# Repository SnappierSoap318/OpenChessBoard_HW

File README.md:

# OpenChessBoard_HW

## Overview
- OpenChessBoard_HW is an open-source hardware project aimed at creating a digital chessboard.
- This project includes the design and schematics for the main board, which can be used to build a functional chessboard.
- This project is derived from [OPEN_CHESS_BOARD](https://openchessboard.com/index.php/2023/03/21/the-openchessboard-design/)
- This project aims to make the design of the board more modular and tileable for ease of manufacturing

## Features
- Single tile design (make 32 white PCB's and 32 Black PCB's and you are done!)
- Uses the Arduino Nano ESP32 as the uP
- Least amount of pins used

## Getting Started
To get started with this project, follow these steps:
1. Clone the repository:
```bash
git clone https://github.com/SnappierSoap318/OpenChessBoard_HW.git
cd OpenChessBoard_HW
```
2. Open in KiCAD 7.0 or above.

## Contribution Guidelines 
If you'd like to contribute, please fork the repository and make a pull request and put the changes you have made as screenshots.

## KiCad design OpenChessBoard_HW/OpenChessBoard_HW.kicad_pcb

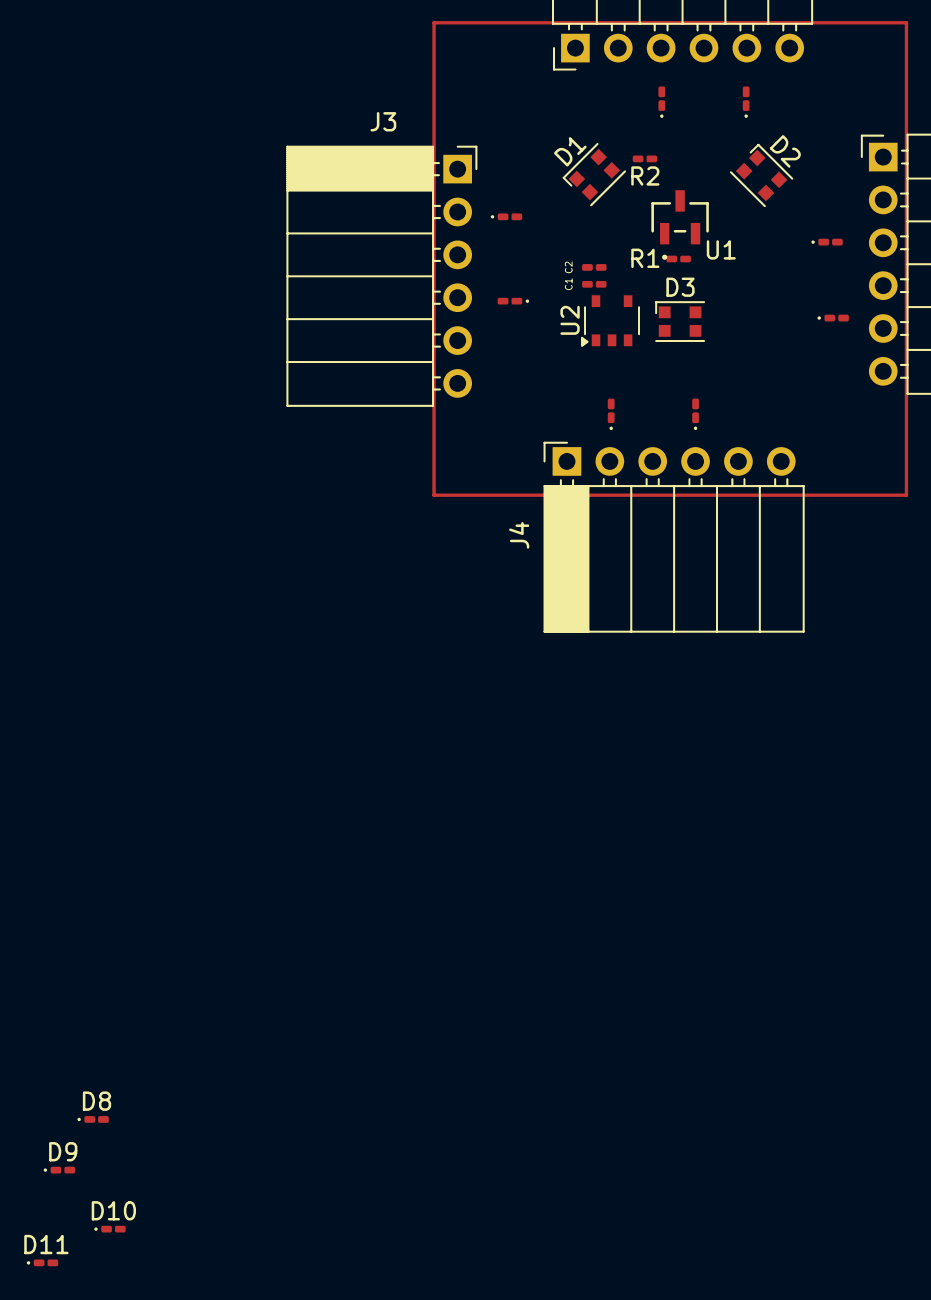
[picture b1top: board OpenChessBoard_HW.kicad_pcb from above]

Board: 2 copper layers, 25 parts (0 on the bottom side), 10 nets, no tracks yet.

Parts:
C1: 100pF; C_0201_0603Metric_Pad0.64x0.40mm_HandSolder
C2: 0.01uF; C_0201_0603Metric_Pad0.64x0.40mm_HandSolder
D1, D2, D3: WS2812B-2020; LED_WS2812B-2020_PLCC4_2.0x2.0mm
D4, D5, D6, D7, D8, D9, D10, D11, D12, D13, D14, D15: D; D_0201_0603Metric_Pad0.64x0.40mm_HandSolder
J1, J2: Conn_01x06_Pin; PinHeader_1x06_P2.54mm_Horizontal
J3, J4: Conn_01x06_Socket; PinSocket_1x06_P2.54mm_Horizontal
R1: 10k; R_0201_0603Metric_Pad0.64x0.40mm_HandSolder
R2: 330R; R_0201_0603Metric_Pad0.64x0.40mm_HandSolder
U1: AH3572-SA-7; SOT23_AH3572-SA-7_DIO
U2: 74LVC1G79; TSOP-5_1.65x3.05mm_P0.95mm

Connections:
+5V: C1.1, C2.1, D1.4 (VDD), D2.4 (VDD), D3.4 (VDD), J1.2, J2.2, J3.5, J4.5, U2.5 (VCC)
CLK: D4.1 (K), D4.2 (A), D5.1 (K), D5.2 (A), D6.1 (K), D6.2 (A), D7.1 (K), D7.2 (A), J1.3, J2.3, J3.4, J4.4, U2.2 (C)
EN: D8.1 (K), D8.2 (A), D9.1 (K), D9.2 (A), D10.1 (K), D10.2 (A), D11.1 (K), D11.2 (A), J1.4, J2.4, J3.3, J4.3
EN_OUT: R1.1, U1.1 (VDD), U2.4 (Q)
GND: C1.2, C2.2, D1.2 (VSS), D2.2 (VSS), D3.2 (VSS), J1.1, J2.1, J3.6, J4.6, U1.2 (GND), U2.3 (GND)
Hallout: J1.6, J2.6, J3.1, J4.1, R1.2, U1.3 (OUTPUT)
LED: D12.1 (K), D12.2 (A), D13.1 (K), D13.2 (A), D14.1 (K), D14.2 (A), D15.1 (K), D15.2 (A), J1.5, J2.5, J3.2, J4.2
unnamed: D1.3 (DIN), R2.2
unnamed: D1.1 (DOUT), D2.3 (DIN)
unnamed: D2.1 (DOUT), D3.3 (DIN)

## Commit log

2024-12-14 Inital Commit
2024-12-24 Added Basic Tile layout and Main Board
2024-12-24 Populated Main board Schematic
2024-12-25 Update Main board to use 74HCT164 instead of 595
